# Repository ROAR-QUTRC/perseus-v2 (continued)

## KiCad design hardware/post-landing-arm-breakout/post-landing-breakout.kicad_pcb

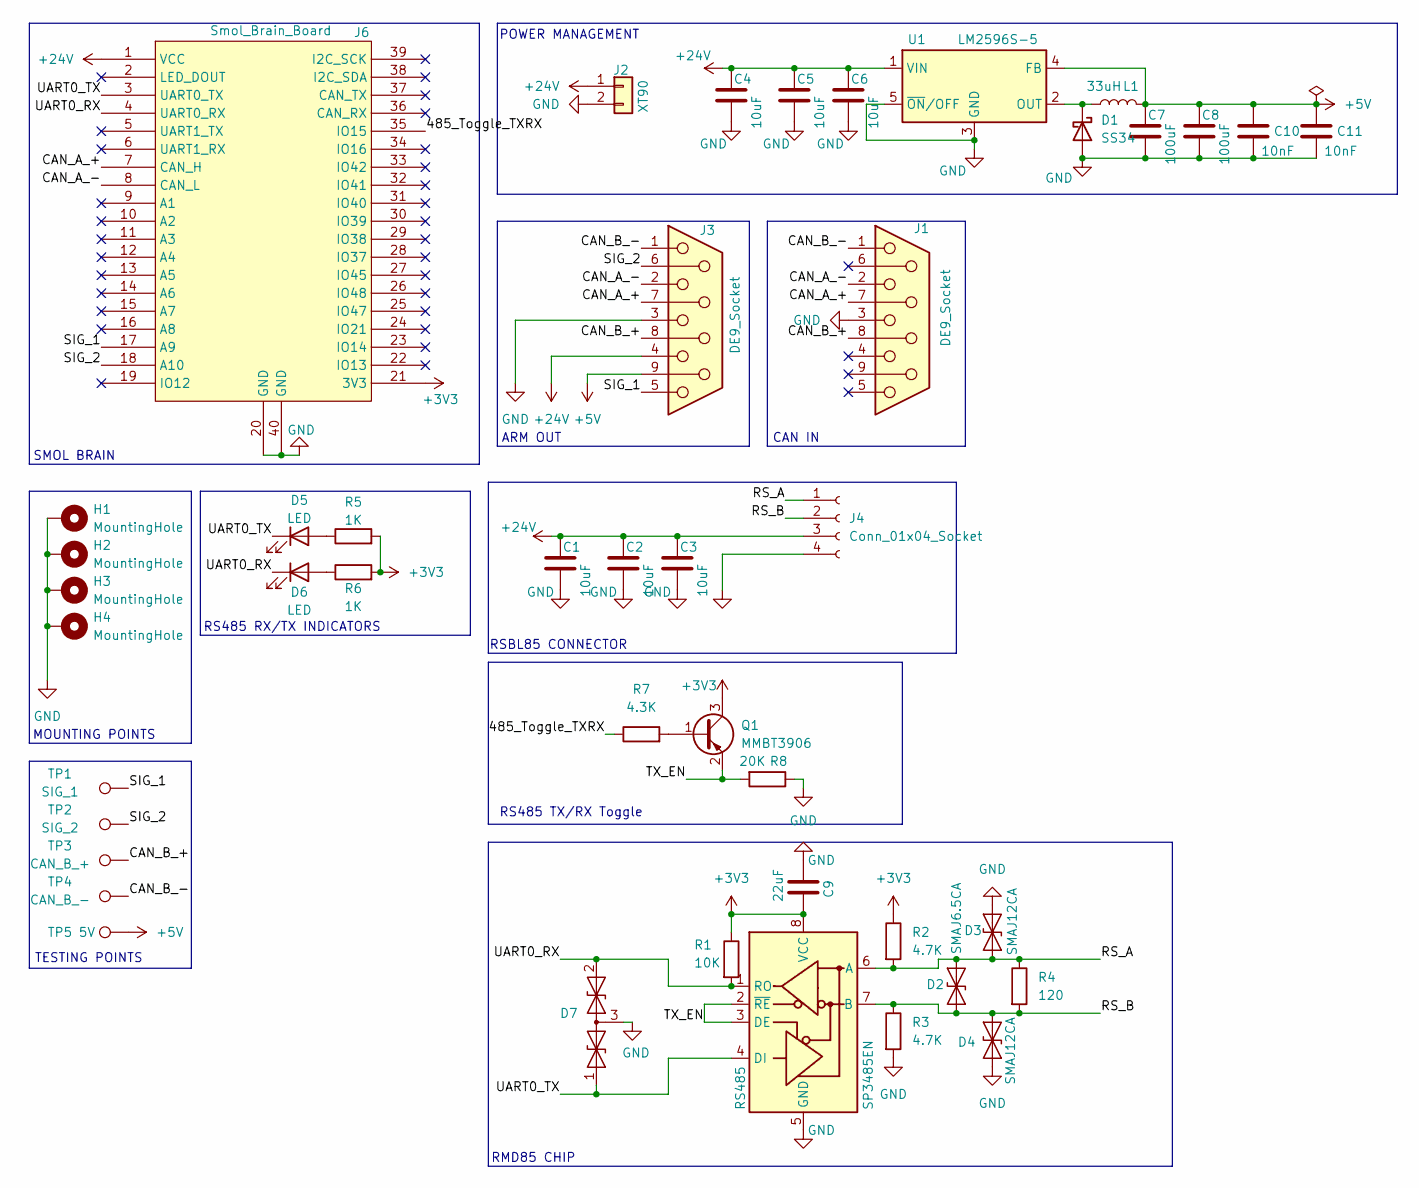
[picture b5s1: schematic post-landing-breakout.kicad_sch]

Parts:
C1, C2, C3, C4, C5, C6: 10uF; C_1206_3216Metric
C7, C8: 100uF; C_Elec_6.3x5.8
C9: 22uF; C_0805_2012Metric_Pad1.18x1.45mm_HandSolder
C10, C11: 10nF; C_0603_1608Metric
D1: SS34; D_SMA
D2: SMAJ6.5CA; D_SMA
D3, D4: SMAJ12CA; D_SMA
D5, D6: LED; LED_0805_2012Metric_Pad1.15x1.40mm_HandSolder
D7: SM712_SOT23; SOT-23
H1, H2, H3, H4: MountingHole; MountingHole_3.2mm_M3_Pad_Via
J1, J3: DE9_Socket; DSUB-9_Socket_Horizontal_P2.77x2.84mm_EdgePinOffset4.94mm_H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
J2: XT90; AMASS_XT90PW-M_1x02_P10.90mm_Horizontal
J4: Conn_01x04_Socket; JST_VH_B4P-VH_4x3.96mm_Vertical
J6: Smol_Brain_Board
L1: 33uH; L_Vishay_IHLP-5050
Q1: MMBT3906; SOT-23
R1: 10K; R_0805_2012Metric_Pad1.20x1.40mm_HandSolder
R2, R3: 4.7K; R_0805_2012Metric_Pad1.20x1.40mm_HandSolder
R4: 120; R_0805_2012Metric_Pad1.20x1.40mm_HandSolder
R5, R6: 1K; R_0805_2012Metric_Pad1.20x1.40mm_HandSolder
R7: 4.3K; R_0805_2012Metric_Pad1.20x1.40mm_HandSolder
R8: 20K; R_0805_2012Metric_Pad1.20x1.40mm_HandSolder
RS485: SP3485EN; SOIC-8_3.9x4.9mm_P1.27mm
TP1: SIG_1; TestPoint_THTPad_1.5x1.5mm_Drill0.7mm
TP2: SIG_2; TestPoint_THTPad_1.5x1.5mm_Drill0.7mm
TP3: CAN_B_+; TestPoint_THTPad_1.5x1.5mm_Drill0.7mm
TP4: CAN_B_-; TestPoint_THTPad_1.5x1.5mm_Drill0.7mm
TP5: 5V; TestPoint_THTPad_1.5x1.5mm_Drill0.7mm
U1: LM2596S-5; TO-263-5_TabPin3

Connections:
+3V3: C9.1, J6.21 (3V3), Q1.3 (C), R1.1, R2.1, R5.2, R6.2, RS485.8 (VCC)
+5V: C7.1, C8.1, C10.1, C11.1, J3.9, L1.2, TP5.1, U1.4 (FB)
+24V: C1.1, C2.1, C3.1, C4.1, C5.1, C6.1, J2.1, J3.4, J4.3, J6.1 (VCC), U1.1 (VIN)
/485_Toggle_TXRX: J6.35 (IO15), R7.1
/CAN_A_+: J1.7, J3.7, J6.7 (CAN_H)
/CAN_A_-: J1.2, J3.2, J6.8 (CAN_L)
/CAN_B_+: J1.8, J3.8, TP3.1
/CAN_B_-: J1.1, J3.1, TP4.1
/RS_A: D2.2 (A2), D3.1 (A1), J4.1, R2.2, R4.1, RS485.6 (A)
/RS_B: D2.1 (A1), D4.1 (A1), J4.2, R3.1, R4.2, RS485.7 (B)
/SIG_1: J3.5, J6.17 (A9), TP1.1
/SIG_2: J3.6, J6.18 (A10), TP2.1
/TX_EN: Q1.2 (E), R8.2, RS485.2 (~RE), RS485.3 (DE)
/UART0_RX: D6.1 (K), D7.2 (A2), J6.4 (UART0_RX), R1.2, RS485.1 (RO)
/UART0_TX: D5.1 (K), D7.1 (A1), J6.3 (UART0_TX), RS485.4 (DI)
GND: C1.2, C2.2, C3.2, C4.2, C5.2, C6.2, C7.2, C8.2, C9.2, C10.2, C11.2, D1.2 (A), D3.2 (A2), D4.2 (A2), D7.3 (common), H1.1, H2.1, H3.1, H4.1, J1.3, J2.2, J3.3, J4.4, J6.20 (GND), J6.40 (GND), R3.2, R8.1, RS485.5 (GND), U1.3 (GND), U1.5 (~ON/OFF)
unnamed: D1.1 (K), L1.1, U1.2 (OUT)
unnamed: D5.2 (A), R5.1
unnamed: D6.2 (A), R6.1
unnamed: Q1.1 (B), R7.2

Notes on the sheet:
MOUNTING POINTS
CAN IN
SMOL BRAIN
ARM OUT
RSBL85 CONNECTOR
POWER MANAGEMENT
TESTING POINTS
RMD85 CHIP
RS485 TX/RX Toggle
RS485 RX/TX INDICATORS

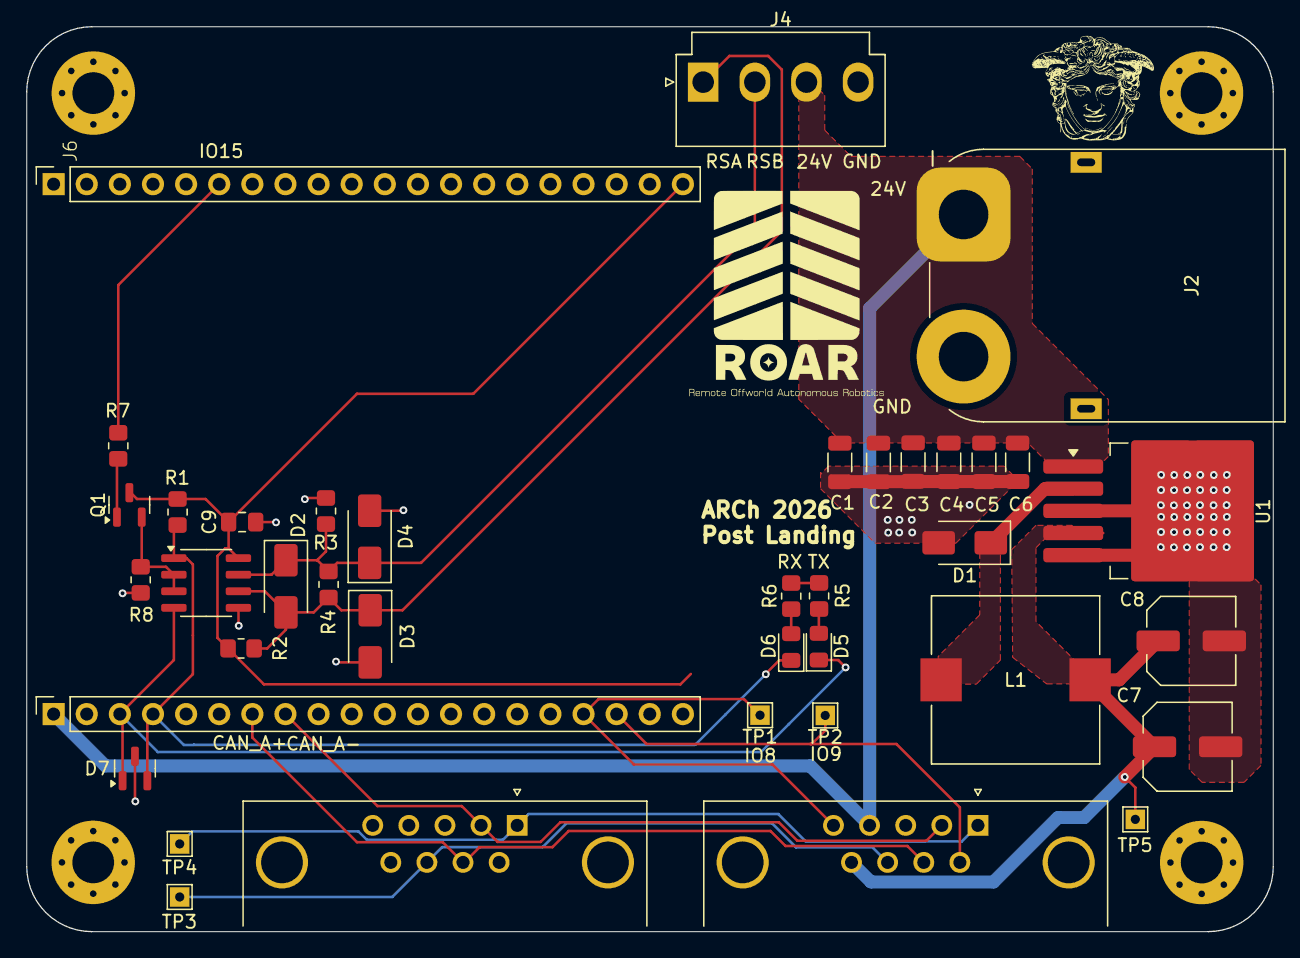
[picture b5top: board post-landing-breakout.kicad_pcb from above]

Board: 2 copper layers, 95.6 x 69.4 mm, 42 parts (0 on the bottom side), 20 nets.

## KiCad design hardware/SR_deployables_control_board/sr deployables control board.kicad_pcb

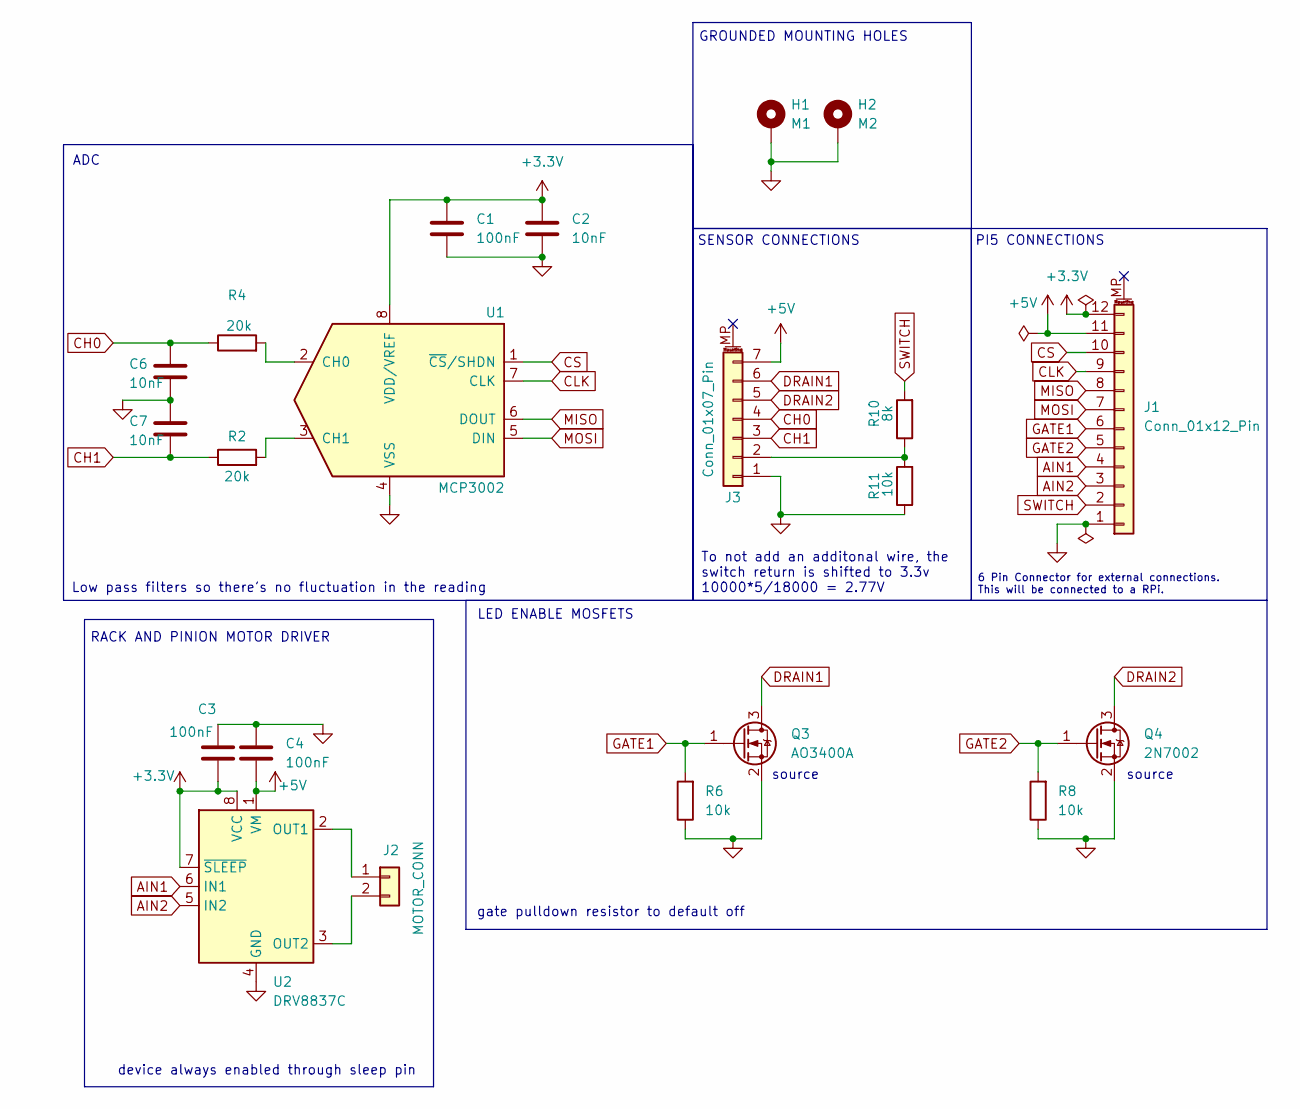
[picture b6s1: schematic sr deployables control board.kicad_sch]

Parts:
C1, C3, C4: 100nF; C_0805_2012Metric_Pad1.18x1.45mm_HandSolder
C2, C6, C7: 10nF; C_0805_2012Metric_Pad1.18x1.45mm_HandSolder
H1: M1; MountingHole_3.2mm_M3_Pad_Via
H2: M2; MountingHole_3.2mm_M3_Pad_Via
J1: Conn_01x12_Pin; JST_ZH_S12B-ZR-SM4A-TF_1x12-1MP_P1.50mm_Horizontal
J2: MOTOR_CONN; JST_XH_B2B-XH-A_1x02_P2.50mm_Vertical
J3: Conn_01x07_Pin; JST_ZH_S7B-ZR-SM4A-TF_1x07-1MP_P1.50mm_Horizontal
Q3: AO3400A; SOT-23_Handsoldering
Q4: 2N7002; SOT-23_Handsoldering
R2, R4: 20k; R_0805_2012Metric_Pad1.20x1.40mm_HandSolder
R6, R8, R11: 10k; R_0805_2012Metric_Pad1.20x1.40mm_HandSolder
R10: 8k; R_0805_2012Metric_Pad1.20x1.40mm_HandSolder
U1: MCP3002; DIP-8_W7.62mm
U2: DRV8837C; WSON-8-1EP_2x2mm_P0.5mm_EP0.9x1.6mm

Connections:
+3.3V: C1.1, C2.1, C3.2, J1.12, U1.8 (VDD/VREF), U2.7 (~SLEEP), U2.8 (VCC)
+5V: C4.2, J1.11, J3.7, U2.1 (VM)
AIN1: J1.4, U2.6 (IN1)
AIN2: J1.3, U2.5 (IN2)
CH0: C6.1, J3.4, R4.1
CH1: C7.2, J3.3, R2.1
CLK: J1.9, U1.7 (CLK)
CS: J1.10, U1.1 (~CS/SHDN)
DRAIN1: J3.6, Q3.3 (D)
DRAIN2: J3.5, Q4.3 (D)
GATE1: J1.6, Q3.1 (G), R6.2
GATE2: J1.5, Q4.1 (G), R8.2
GND: C1.2, C2.2, C3.1, C4.1, C6.2, C7.1, H1.1, H2.1, J1.1, J3.1, Q3.2 (S), Q4.2 (S), R6.1, R8.1, R11.1, U1.4 (VSS), U2.4 (GND), U2.9 (GND)
MISO: J1.8, U1.6 (DOUT)
MOSI: J1.7, U1.5 (DIN)
unnamed: J2.1, U2.2 (OUT1)
unnamed: J2.2, U2.3 (OUT2)
unnamed: J3.2, R10.1, R11.2
unnamed: R4.2, U1.2 (CH0)
unnamed: R2.2, U1.3 (CH1)
SWITCH: J1.2, R10.2

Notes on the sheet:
PI5 CONNECTIONS
gate pulldown resistor to default off
device always enabled through sleep pin
source
To not add an additonal wire, the switch return is shifted to 3.3v 10000*5/18000 = 2.77V
SENSOR CONNECTIONS
ADC
RACK AND PINION MOTOR DRIVER
Low pass filters so there's no fluctuation in the reading
6 Pin Connector for external connections. This will be connected to a RPi.
GROUNDED MOUNTING HOLES
LED ENABLE MOSFETS

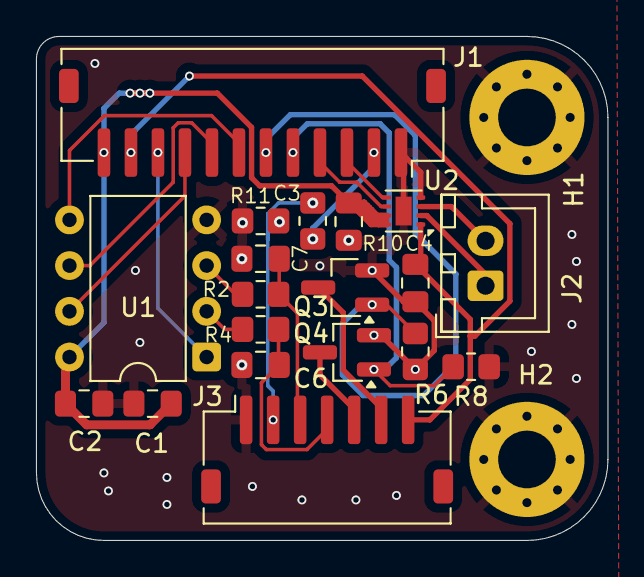
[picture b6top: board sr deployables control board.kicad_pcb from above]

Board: 2 copper layers, 31.8 x 28.0 mm, 21 parts (0 on the bottom side), 21 nets.

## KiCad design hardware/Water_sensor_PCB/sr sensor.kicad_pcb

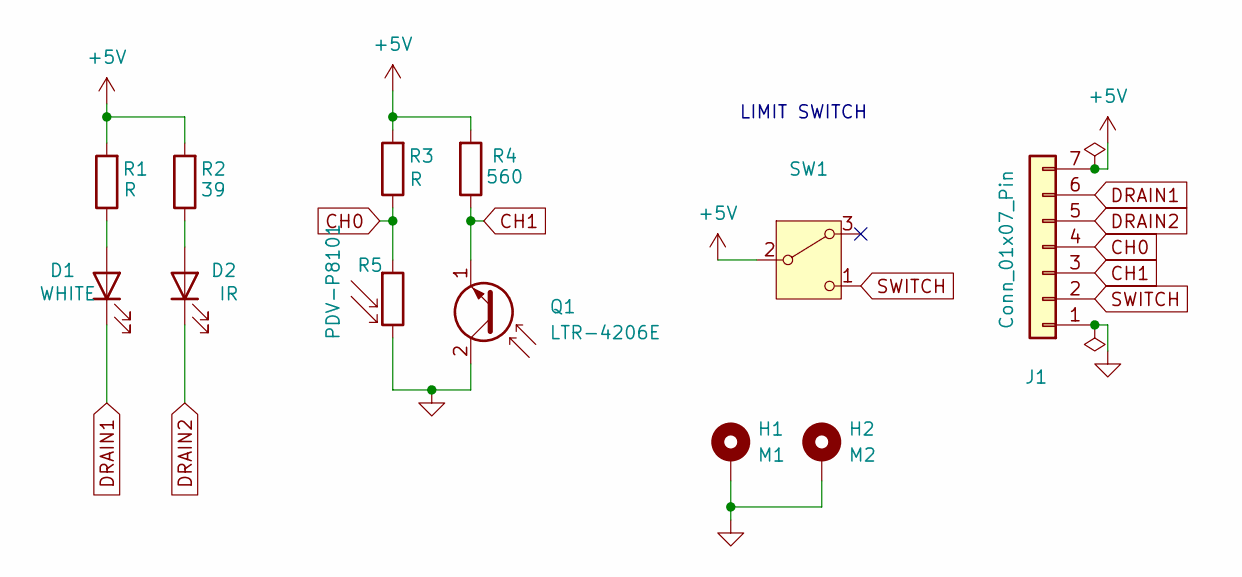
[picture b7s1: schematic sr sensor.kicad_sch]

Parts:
D1: WHITE; LED_D3.0mm_Clear
D2: IR; LED_D3.0mm_Clear
H1: M1; MountingHole_3.2mm_M3_Pad_Via
H2: M2; MountingHole_3.2mm_M3_Pad_Via
J1: Conn_01x07_Pin; JST_ZH_B7B-ZR_1x07_P1.50mm_Vertical
Q1: LTR-4206E; LED_D3.0mm
R1, R3: R; R_0805_2012Metric_Pad1.20x1.40mm_HandSolder
R2: 39; R_0805_2012Metric_Pad1.20x1.40mm_HandSolder
R4: 560; R_0805_2012Metric_Pad1.20x1.40mm_HandSolder
R5: PDV-P8101; R_LDR_5.1x4.3mm_P3.4mm_Vertical
SW1: SW_Nidec_CAS-120A1; JST_ZH_B3B-ZR_1x03_P1.50mm_Vertical

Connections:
+5V: J1.7, R1.2, R2.2, R3.2, R4.2, SW1.2 (B)
CH0: J1.4, R3.1, R5.1
CH1: J1.3, Q1.1 (E), R4.1
DRAIN1: D1.1 (K), J1.6
DRAIN2: D2.1 (K), J1.5
GND: H1.1, H2.1, J1.1, Q1.2 (C), R5.2
unnamed: D1.2 (A), R1.1
unnamed: D2.2 (A), R2.1
SWITCH: J1.2, SW1.1 (C)

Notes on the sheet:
LIMIT SWITCH

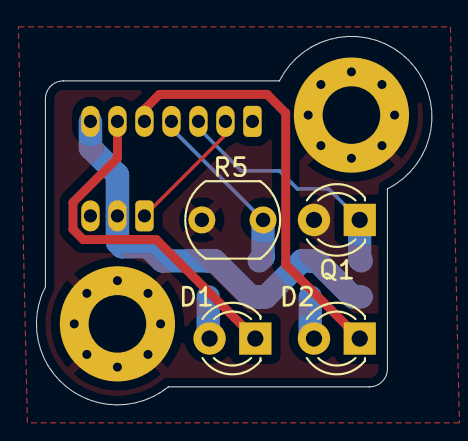
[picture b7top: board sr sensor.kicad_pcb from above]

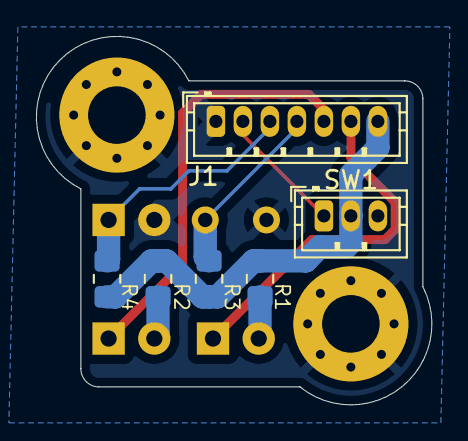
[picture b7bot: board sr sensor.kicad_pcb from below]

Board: 2 copper layers, 22.0 x 20.5 mm, 12 parts (6 on the bottom side), 9 nets.

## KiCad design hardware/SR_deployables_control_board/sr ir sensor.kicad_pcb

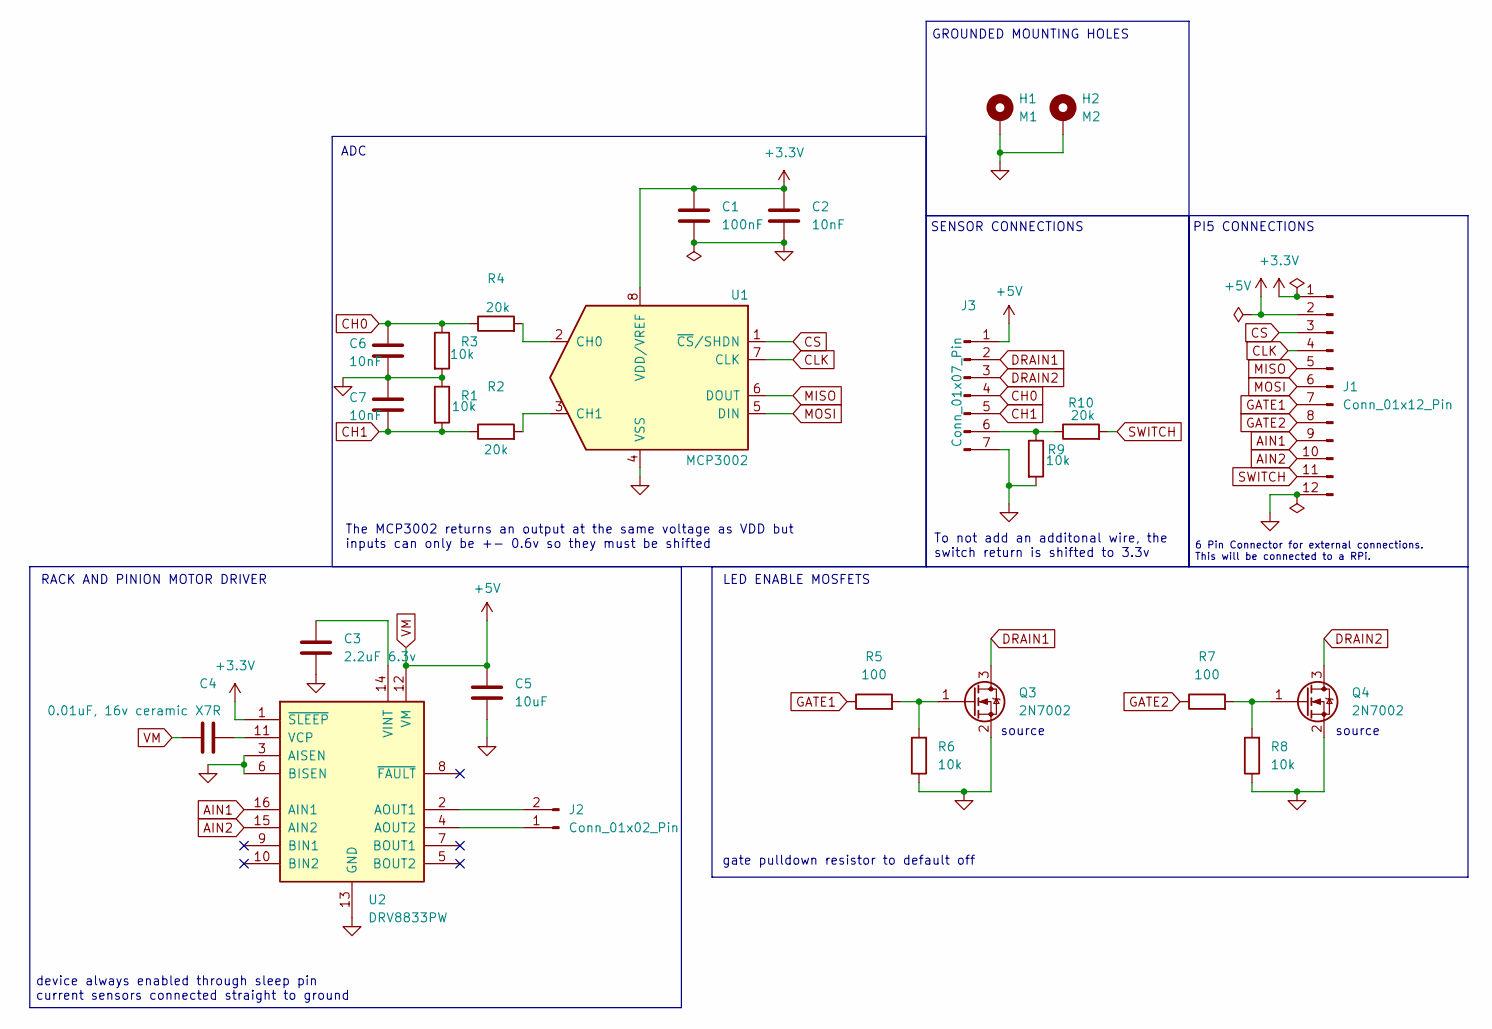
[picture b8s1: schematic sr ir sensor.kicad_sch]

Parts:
C1: 100nF; C_0805_2012Metric_Pad1.18x1.45mm_HandSolder
C2, C6, C7: 10nF; C_0805_2012Metric_Pad1.18x1.45mm_HandSolder
C3: 2.2uF 6.3v; C_0805_2012Metric_Pad1.18x1.45mm_HandSolder
C4: 0.01uF, 16v ceramic X7R; C_0805_2012Metric_Pad1.18x1.45mm_HandSolder
C5: 10uF; C_0805_2012Metric_Pad1.18x1.45mm_HandSolder
H1: M1; MountingHole_2.2mm_M2_Pad_Via
H2: M2; MountingHole_2.2mm_M2_Pad_Via
J1: Conn_01x12_Pin; JST_GH_BM12B-GHS-TBT_1x12-1MP_P1.25mm_Vertical
J2: Conn_01x02_Pin; PinHeader_1x02_P2.54mm_Vertical
J3: Conn_01x07_Pin; JST_EH_B7B-EH-A_1x07_P2.50mm_Vertical
Q3, Q4: 2N7002; SOT-23_Handsoldering
R1, R3, R6, R8, R9: 10k; R_0805_2012Metric_Pad1.20x1.40mm_HandSolder
R2, R4, R10: 20k; R_0805_2012Metric_Pad1.20x1.40mm_HandSolder
R5, R7: 100; R_0805_2012Metric_Pad1.20x1.40mm_HandSolder
U1: MCP3002; DIP-8_W7.62mm
U2: DRV8833PW; TSSOP-16-1EP_4.4x5mm_P0.65mm_EP3x3mm_ThermalVias

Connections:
+3.3V: C1.1, C2.1, J1.1, U1.8 (VDD/VREF), U2.1 (~SLEEP)
AIN1: J1.9, U2.16 (AIN1)
AIN2: J1.10, U2.15 (AIN2)
CH0: C6.1, J3.4, R3.1, R4.1
CH1: C7.2, J3.5, R1.2, R2.1
CLK: J1.4, U1.7 (CLK)
CS: J1.3, U1.1 (~CS/SHDN)
DRAIN1: J3.2, Q3.3 (D)
DRAIN2: J3.3, Q4.3 (D)
GATE1: J1.7, R5.1
GATE2: J1.8, R7.1
GND: C1.2, C2.2, C3.2, C5.2, C6.2, C7.1, H1.1, H2.1, J1.12, J3.7, Q3.2 (S), Q4.2 (S), R1.1, R3.2, R6.1, R8.1, R9.2, U1.4 (VSS), U2.3 (AISEN), U2.6 (BISEN), U2.13 (GND)
MISO: J1.5, U1.6 (DOUT)
MOSI: J1.6, U1.5 (DIN)
unnamed: J2.1, U2.4 (AOUT2)
unnamed: J2.2, U2.2 (AOUT1)
unnamed: J3.6, R9.1, R10.1
unnamed: Q3.1 (G), R5.2, R6.2
unnamed: Q4.1 (G), R7.2, R8.2
unnamed: R4.2, U1.2 (CH0)
unnamed: R2.2, U1.3 (CH1)
unnamed: C4.2, U2.11 (VCP)
unnamed: C3.1, U2.14 (VINT)
SWITCH: J1.11, R10.2
VM: C4.1, C5.1, J1.2, J3.1, U2.12 (VM)

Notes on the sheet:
PI5 CONNECTIONS
gate pulldown resistor to default off
device always enabled through sleep pin current sensors connected straight to ground
source
To not add an additonal wire, the switch return is shifted to 3.3v
SENSOR CONNECTIONS
ADC
RACK AND PINION MOTOR DRIVER
6 Pin Connector for external connections. This will be connected to a RPi.
GROUNDED MOUNTING HOLES
The MCP3002 returns an output at the same voltage as VDD but inputs can only be +- 0.6v so they must be shifted
LED ENABLE MOSFETS

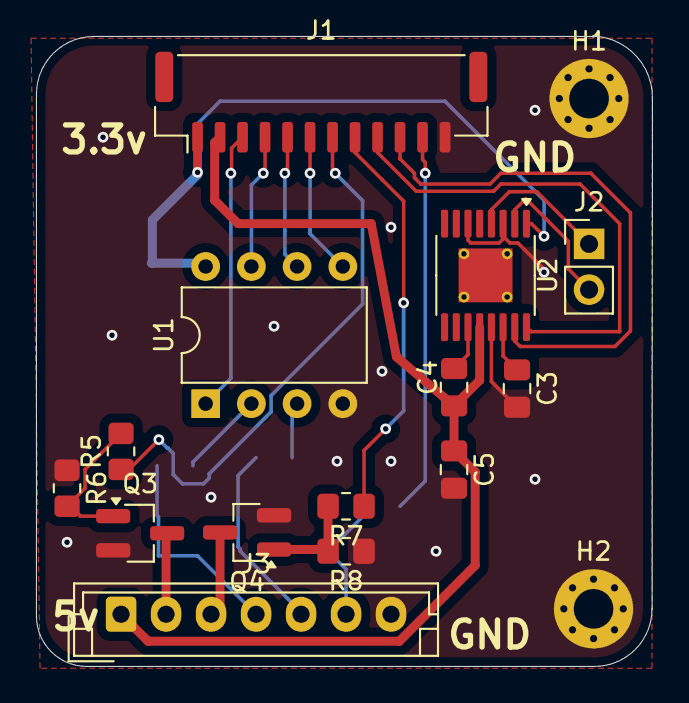
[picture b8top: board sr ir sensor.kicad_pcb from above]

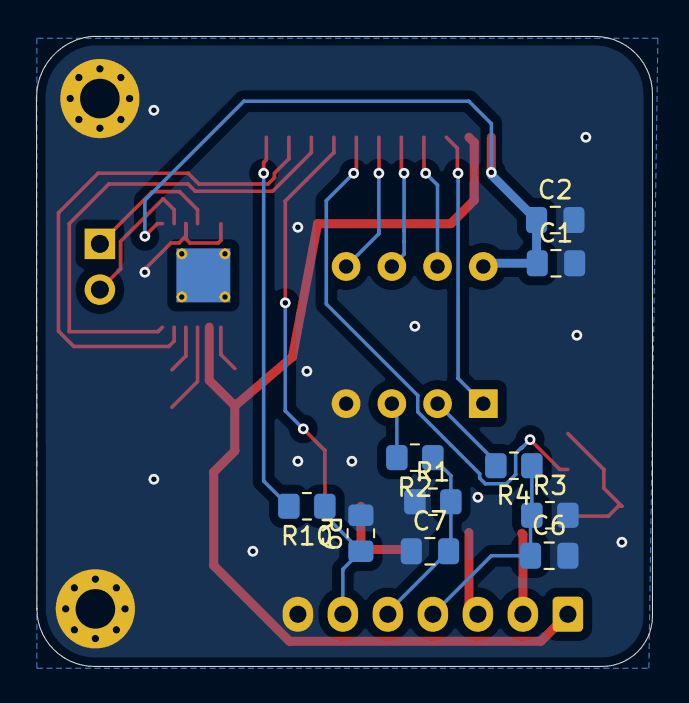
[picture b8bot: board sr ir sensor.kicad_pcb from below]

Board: 2 copper layers, 34.2 x 35.0 mm, 26 parts (10 on the bottom side), 25 nets.

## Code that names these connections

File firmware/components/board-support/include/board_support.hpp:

#pragma once

#include <driver/gpio.h>

#include <tuple>

/// @brief Board Support Package - contains board-specific constants and configurations
namespace bsp
{
    /**
     * @brief An ordered pair of GPIO pins.
     *
     * When used for a CAN bus or UART, first pin is for TX, and the second is RX.
     * When used for a motor driver, first pin is for A, and the second is for B.
     */
    typedef std::pair<gpio_num_t, gpio_num_t> pin_pair_t;

    constexpr gpio_num_t CAN_TX_PIN = GPIO_NUM_0;
    constexpr gpio_num_t CAN_RX_PIN = GPIO_NUM_11;

    constexpr gpio_num_t I2C_SDA = GPIO_NUM_35;
    constexpr gpio_num_t I2C_SCL = GPIO_NUM_36;

    constexpr gpio_num_t A1 = GPIO_NUM_1;
    constexpr gpio_num_t A2 = GPIO_NUM_2;
    constexpr gpio_num_t A3 = GPIO_NUM_3;
    constexpr gpio_num_t A4 = GPIO_NUM_4;
    constexpr gpio_num_t A5 = GPIO_NUM_5;
    constexpr gpio_num_t A6 = GPIO_NUM_6;
    constexpr gpio_num_t A7 = GPIO_NUM_7;
    constexpr gpio_num_t A8 = GPIO_NUM_8;
    constexpr gpio_num_t A9 = GPIO_NUM_9;
    constexpr gpio_num_t A10 = GPIO_NUM_10;

    void initI2C();
}

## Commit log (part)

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2026-03-27 Working Controller
2026-03-27 chore: Update Nix packaging
2026-03-27 chore: Format and lint
2026-03-27 Added launch file and started Perseus integration
2026-03-27 ROS Node for Light Driver
2026-03-27 Light Ring Firmware
2026-03-27 Added blinking red for CAN health
2026-03-27 Changed to Int8 for controller
2026-03-27 feat: add config file
2026-03-27 colcon build cmake fix
2026-03-27 launch config for comp
2026-03-27 bool to uint8 to remove weird can packets
2026-03-27 SQUASH ME Fixing bms firmware
2026-03-27 feat: Created launch file for gscam, integrating gst cameras
2026-03-27 fix: Using sensor QOS to ensure the camera always updates
2026-03-27 odom-fix
2026-03-28 Feat: added rcb driver to perseus bringup
2026-03-28 feat: fixed heat gradient and reduced noisy along the borders
2026-03-28 feat: disable infrared streams and adjust depth module settings in realsense_launch.yaml
2026-03-28 Feat: add CycloneDDS configuration for network peers
2026-03-28 Fix: update RealSense configuration to disable color and depth streams
2026-03-28 feat: Add CycloneDDS configuration and map files for autonomy architecture
2026-03-28 feat: Update map file path in autonomy launch configuration
2026-03-28 feat: Update EKF configuration and add navigation architecture files
2026-03-28 feat: Update autonomy launch files to include map server and lifecycle manager
2026-03-28 feat: Update EKF configuration file path in autonomy launch
2026-03-28 feat: Add stereo odometry node and configuration
    - Introduced a new executable `stereo_odom_node` in CMakeLists.txt.
    - Added parameters for stereo odometry in `perseus_vision.yaml`, including topics for left and right images, camera info, and odometry settings.
    - Created `stereo_odom.hpp` and `stereo_odom.cpp` to implement the StereoOdom class for processing stereo images and publishing odometry.
    - Implemented a launch file `stereo_odom.launch.py` to facilitate node execution with configurable parameters.
    - Updated `package.xml` to include dependencies for nav_msgs and message_filters.
2026-03-28 feat: correct origin coordinates in aut_arch_2026.yaml
2026-03-28 feat: Add EKF configuration for stereo IMU and update launch file reference
2026-03-28 feat: update controller parameters and remove collision_monitor from launch file
2026-03-28 feat: add DetectAruco action node and include perseus_interfaces dependency
2026-03-28 feat: Update EKF configuration and launch file for improved IMU data handling
2026-03-28 Feat: update CycloneDDS configuration with Dan's Ethernet address
2026-03-28 feat: enhance navigation and light orchestrator configurations with perseus_interfaces dependency
2026-03-28 Formatting
2026-03-28 Changed scaling to 0.5 for moving
2026-03-28 Fixed config
2026-03-28 refactor: remove pointcloud to laserscan converter node from launch file
2026-03-28 Fix: update depth and infrared profiles in RealSense configuration
2026-03-28 fix: update EKF configuration parameters for improved performance
2026-03-28 fix: increase imu0_queue_size for improved data handling
2026-03-28 fix: update EKF configuration parameters for improved performance and stability
2026-03-28 fix: reduce EKF frequency to 20Hz for lower CPU load and update IMU topic
2026-03-28 fix: update IMU topic to corrected data for improved accuracy
2026-03-28 fix: update odom0 topic to use stereo odometry for improved localization
2026-03-28 fix: enable TF publishing for stereo odometry to improve integration with TF tree
2026-03-28 fix: add IMU topic declaration and update EKF config file path for improved localization
2026-03-28 feat: Add --flatten flag for automatic ground-plane compensation
    Fits a least-squares plane to the point cloud and subtracts the tilt
    component from Z, levelling scans captured on sloped terrain.
2026-03-28 feat: Add --raw-points flag to render full point cloud in 3D view
    Bypasses the 120x120 interpolated grid and renders all raw points
    directly, preserving full scan detail. Supports elevation colormap
    and intensity-based greyscale.
2026-03-28 fix: Compute grid colors for mesh modes in 3D render
    The colors variable was only set in the Points branches, causing an
    UnboundLocalError when switching to Wireframe or Solid modes.
2026-03-28 fix: update navigation parameters and launch configurations for improved performance and integration
2026-03-28 feat: Add elevation colour range sliders for real-time adjustment
    Two sliders (min/max) in the sidebar let you clip the elevation
    colour range to focus on lower terrain detail, ignoring peaks.
    Visible only when the elevation layer is active.
2026-03-28 fix: remove unused voxel layer configuration to streamline costmap setup
2026-03-28 fix: update network interface address and adjust EKF frequency for optimized performance
2026-03-28 feat: Enable --flatten and --raw-points by default
    Both flags are now on by default. Use --no-flatten or --no-raw-points
    to disable them.
2026-03-28 feat: Add elevation colour range text inputs to 3D view
    Min/Max text boxes in the 3D OPTIONS sidebar let the user set a
    custom colour range for elevation colouring. Applies to both raw
    point cloud and grid mesh modes.
2026-03-28 fix: update imu0_config to disable additional IMU channels for improved accuracy
2026-03-28 fix: increase imu0_queue_size for improved data handling and update imu_topic for consistency
2026-03-28 feat: change imu topic name
2026-03-28 feat: Add checkbox to hide 3D geometry outside colour range
    When enabled, points outside the min/max range are removed entirely
    (Points mode) or made fully transparent (Wireframe/Solid modes),
    letting the user isolate terrain within the elevation range of interest.
2026-03-28 refactor: remove unused parameters from controller_server for cleaner configuration
2026-03-28 refactor: clean up controller_server parameters and adjust velocity settings for improved performance
2026-03-28 fix: ensure proper formatting and remove unused imports in launch files
2026-03-28 fix: update lidar topic and adjust priority settings in twist_mux configuration
2026-03-28 fix: update network interface address in CycloneDDS configuration
2026-03-28 fix: update navigation topic in twist_mux configuration
2026-03-28 feat:nav2
2026-03-28 fix: update launch configuration for SLAM and navigation parameters
2026-03-28 Controller launched
2026-03-28 fix: remove unused imports from autonomy launch file
2026-03-28 feat: add map configuration and lifecycle manager to autonomy launch file
2026-03-28 fix: update cmd_vel_out_topic for collision_monitor in navigation config files
2026-03-28 feat: add remapping for cmd_vel_smoothed to cmd_vel_out in launch description
2026-03-28 Feat: enable color stream in RealSense configuration
2026-03-28 Feat: enable depth stream and disable infrared streams in RealSense configuration
2026-05-07 feat(text detection): initial integration prototype
2026-05-07 feat(launch + dependency + restructure): followed github outline struct
    - Added a launchfile for the node
    - Added dependencies for message types
    - Restructured the node to reflect https://github.com/orgs/ROAR-QUTRC/projects/1/views/1?pane=issue&itemId=116353845&issue=ROAR-QUTRC%7Cperseus-v2%7C203
2026-05-07 fix(text detection): fixed imutils.object detection import
2026-05-07 fix(treefmt): added neural network to format exclusion
2026-05-07 refactor(perseus text detection): let nix-packages.sh format
2026-05-07 feat: Included launch file in setup.py
2026-05-07 fix(shell): removed imutil from nix packages
2026-05-07 chore: Update `treefmt.toml`
2026-05-09 fix: Removed udev for librealsense on darwin
2026-05-09 fix: Removed libcap from realtime-tools on darwin
2026-05-09 fix: Removed groot2 from darwin workspace
2026-05-09 Updated flake
2026-05-22 test(hi-can): Add gtest suite for serialization primitives and VESC group
    Finishes the gtest scaffolding that had been left commented out in
    software/shared/hi-can/CMakeLists.txt and gives every device that builds
    on the hi-can serialization primitives a regression baseline to copy.
    30 tests, 100% passing:
    - serializable_test.cpp covers the foundational primitives
    (scaled_int32_t, scaled_int16_t, SimpleSerializable<T>, wrapped_value_t)
2026-05-22 test(hi-can): Address self-review findings before opening PR
    Acts on the critical review of the initial test commit:
    - Extract shared helpers into test_helpers.hpp (be32, be16, concat) and
    mock_can_interface.hpp (FifoCanInterface). Both files cast to unsigned
    before shifting so the right-shifts are unambiguously logical, not
    implementation-defined arithmetic on signed integers.
    - Use handle_receive() in the VESC inject() helper so deserialize tests
2026-06-03 feat: Update flake.lock
2026-06-09 feat: Add Mission Zero (Selene Base Rescue) mission package
    - perseus_lite_missions: orchestrator + map-quality and goal-reached
    checker nodes, mission descriptor, broken/reference SLAM and Nav2
    configs, mission_zero launch file
    - selene_base.sdf world for perseus_lite_simulation
    - Forward gz_world and initial_pose_* args through perseus_sim.launch.py
    so mission worlds and spawn poses actually reach gazebo.launch.py
2026-06-14 chore: Add vikit-common and vikit-ros to development packages
2026-06-14 chore: Add vikit-common and vikit-ros packages to overlay.nix
2026-06-14 chore: Update vikit packages to inherit sophus and adjust C++ standard for compatibility
2026-06-19 fix(lunar_pcd_viewer): remove unused cam variable
    ruff F841: `cam = self._gl_view.cameraPosition()` in _render_3d was never
    used; camera state is preserved via the `opts` dict copy (center/distance/
    elevation/azimuth/fov), which is what the restore logic reads. Removing the
    dead assignment unblocks the Format and lint CI check.
2026-06-21 feat: Added watch_dir to envrc to reload env if any nix file is changed
2026-06-28 build(pixi): get core workspace building in the default env
    Pin two dependency versions that the unconstrained '*' resolved wrongly, and
    verify the build:
    - libboost-devel pinned to 1.88: Boost 1.90 (pulled by ros2-distro-mutex 0.15)
    dropped the boost_system component config, breaking perseus_lite_hardware's
    find_package(Boost COMPONENTS system). 1.88 restores it and aligns all envs.
    - setuptools pinned <80: colcon's ament_python --symlink-install runs
2026-06-28 build(pixi): build perseus_sensors in default; move vision to ml env
    - perseus_sensors now builds in the default env unchanged: its CMake
    add_subdirectory fallback compiles the software/shared libs (simple-networking
    -> fd-wrapper, ptr-wrapper) in-tree, so no package.xml or conda recipes are
    needed for the shared C++ libraries.
    - perseus_vision moves to the machine-learning env: conda-forge ships
    onnxruntime-cpp (the C++ runtime it needs) only in CUDA builds, matching the
2026-06-28 chore(nix): remove Nix build system; document Pixi in CLAUDE.md
    Remove the entire Nix build/packaging layer now that Pixi reaches parity for
    the workspace build, tests, format, and docs:
    - flake.nix, flake.lock, default.nix, shell.nix, treefmt.nix, nix/
    - packages/ (groot2, open3d overlays), docs/default.nix, docs/nix/
    - software/{default,overlay}.nix, native/overlay.nix, shared/**/default.nix,
    shared/overlay.nix
2026-06-28 docs(pixi): update conda-recipe backlog — SLAM/coverage pkgs dropped
    The upstream lidarslam_ros2/ndt-omp-ros2/opennav-coverage/fields2cover packages
    are not referenced anywhere in the lite workspace, so they are dropped rather
    than ported. Only twist_stamper, groot2, and optional RealSense remain as
    deferred items; shared C++ libs and Open3D need no recipes.
